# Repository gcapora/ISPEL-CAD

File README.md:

# Diseño de circuitos impresos del proyecto ISPEL

Autores: Guillermo Caporaletti y Alejandro Santari.
ISPEL Beta, Revisión 1.

En esta carpeta están los diseños de las placas del prototipo Beta 2024 de la Interfaz de Señales para Prácticas Educativas de Laboratorio (ISPEL). 

## Estructura de carpetas

- Docs: Incluye documentos de elaboración propia. Incluye listado de materiales.
- Info: Incluye bibliografía, hojas de datos, referencias y demás información que no es elaboración propia.
- PCB_Frente: PCB de botones y leds del frente del gabinete.
- PCB_Principal: PCB principal, sobre la cual va montada la placa Nuleao-144 de STM.

## Versiones

- Primera versión Beta corresponde al diseño presentado como parte del trabajo final de la Carrera de Especialización en Sistemas Embebidos de la FIUBA: [Versión 1 Beta](https://github.com/gcapora/ISPEL-CAD/releases/tag/v1-beta)

## Comentarios

- El diseño en PCB_Principal fue corregido tras construir el primer prototipo.
- Los archivos de PCB_Frente son orientativos y deben ser corregidos.

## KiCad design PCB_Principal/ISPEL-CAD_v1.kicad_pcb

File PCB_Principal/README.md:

Aquí van los archivos del proyecto PLACA PRINCIPAL que incluye:
- Fuente y tensión de referencia
- Amplificadores
- Búferes de entrada
- Señal de prueba

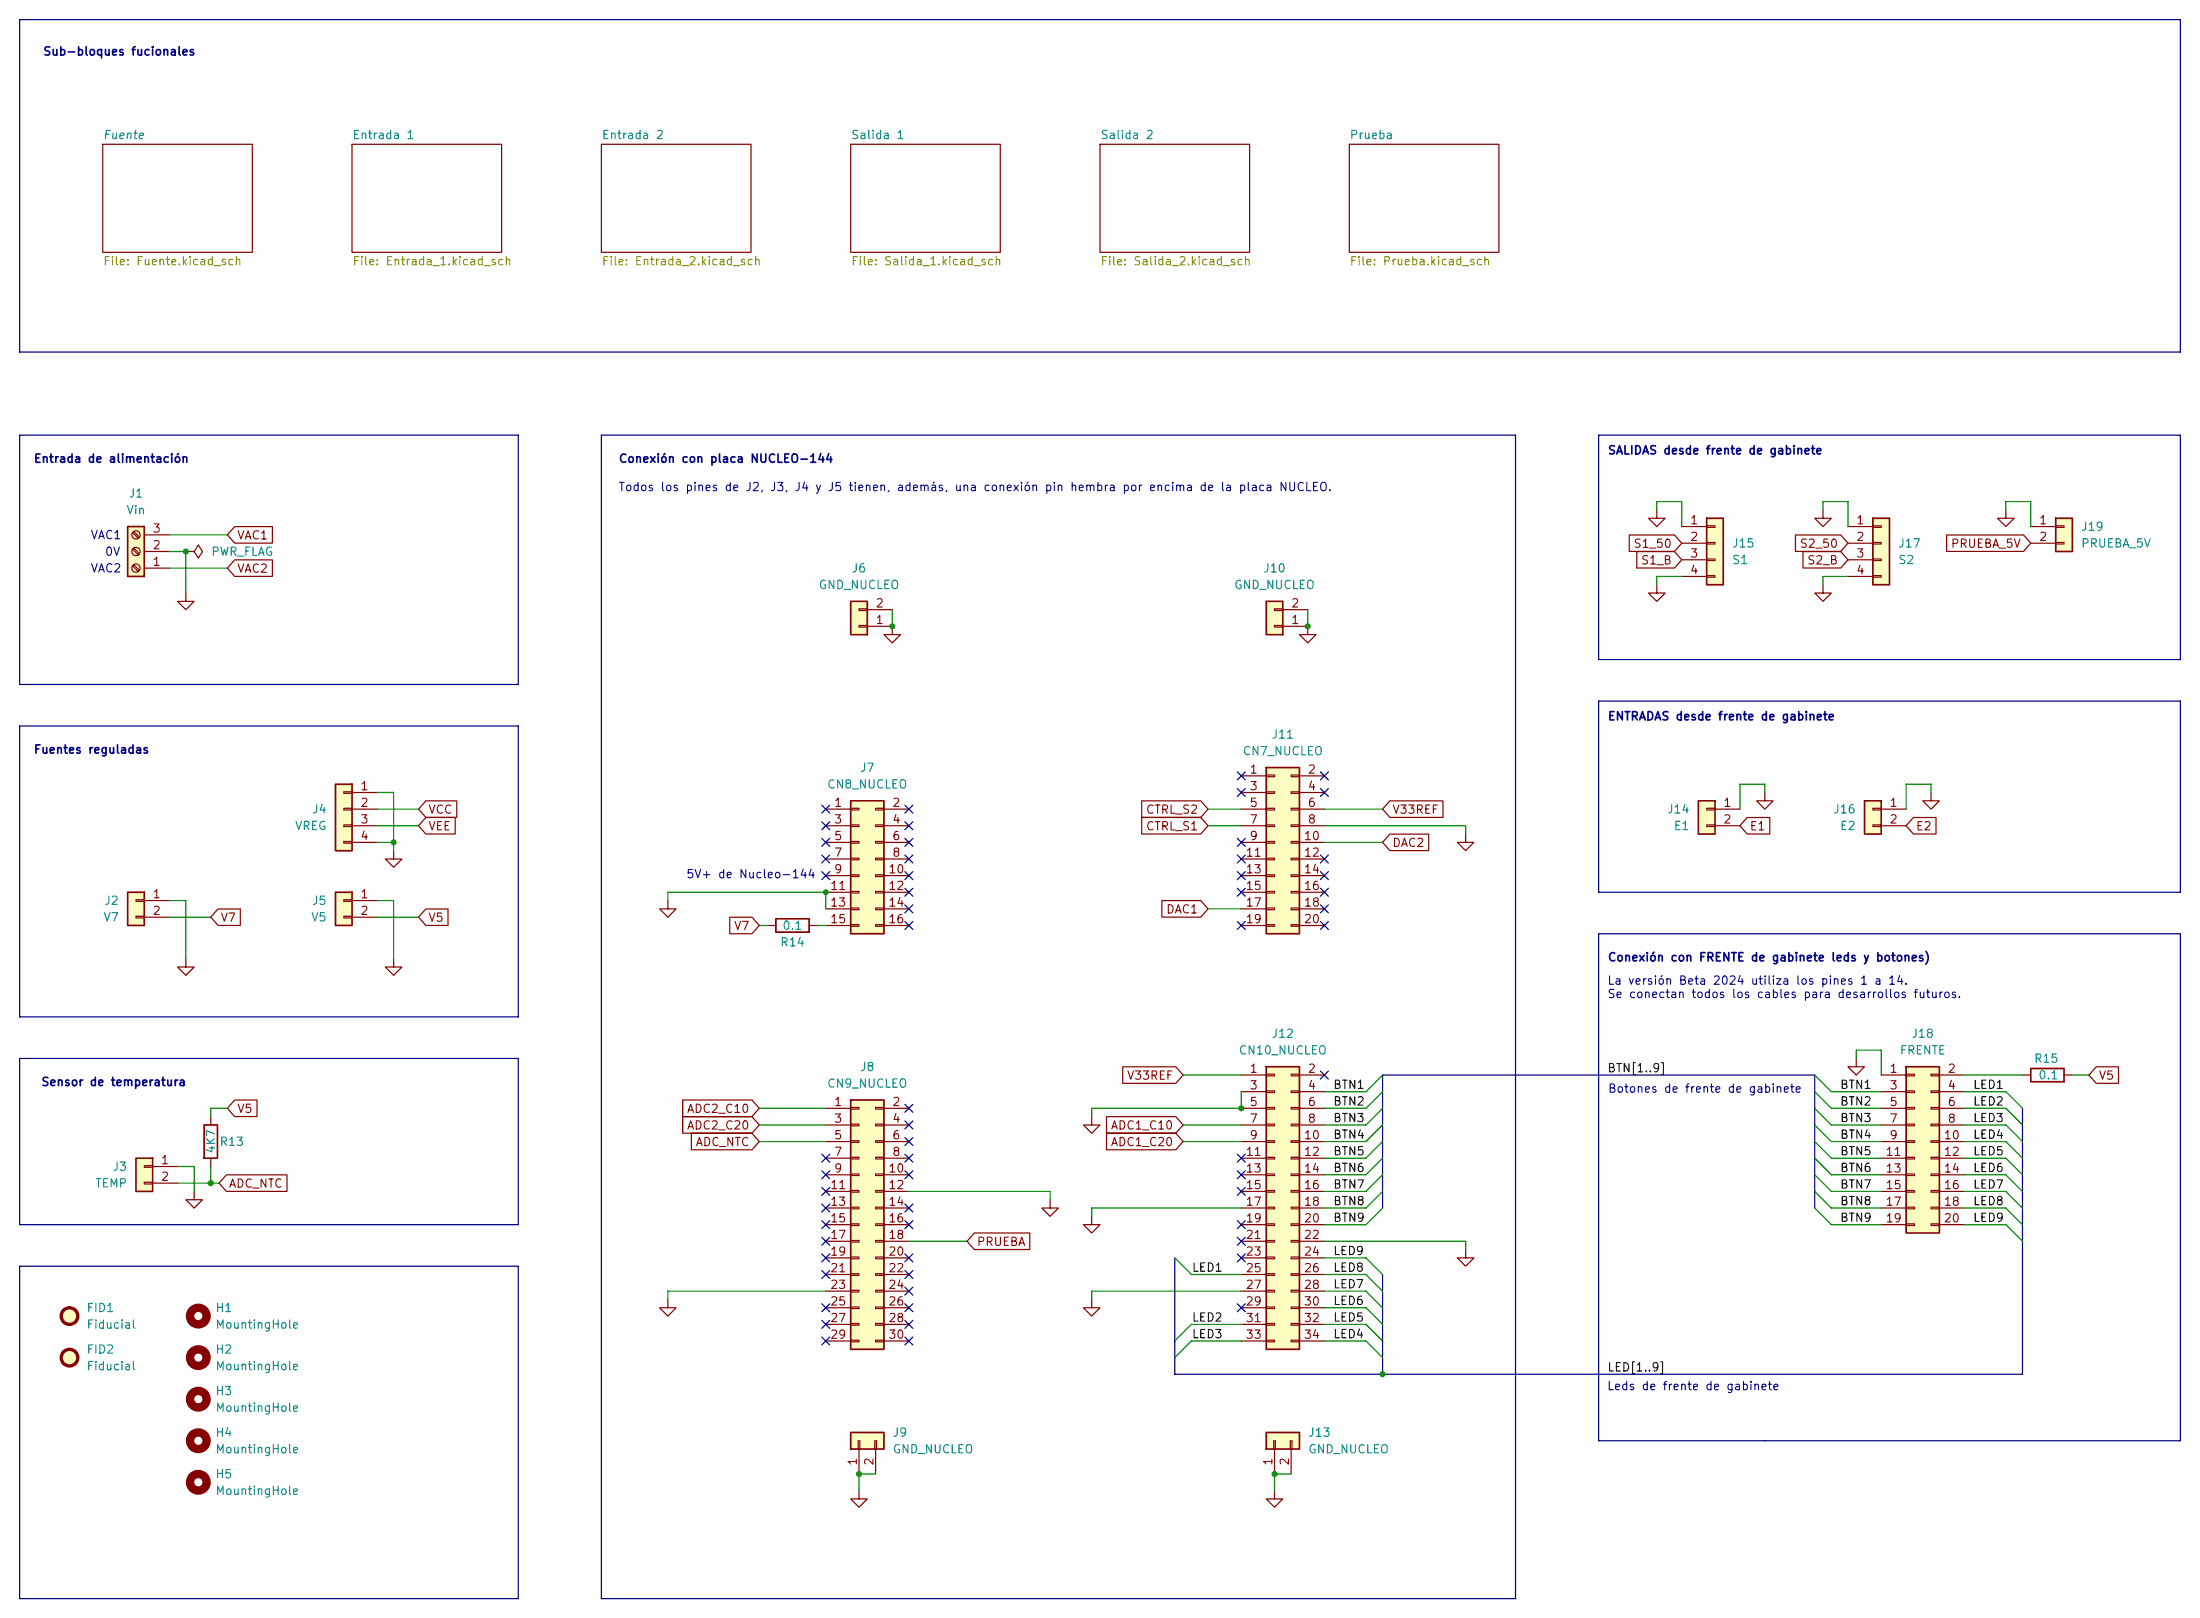
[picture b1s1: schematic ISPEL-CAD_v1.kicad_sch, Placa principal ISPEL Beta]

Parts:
FID1, FID2: Fiducial; Fiducial_1mm_Mask3mm
H1, H2, H3, H4, H5: MountingHole; MountingHole_3.2mm_M3
J1: Vin; TerminalBlock_Phoenix_MKDS-1,5-3-5.08_1x03_P5.08mm_Horizont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
J2: V7; PinSocket_1x02_P2.54mm_Vertical
J3: TEMP; PinHeader_1x02_P2.54mm_Vertical
J4: VREG; PinSocket_1x04_P2.54mm_Vertical
J5: V5; PinSocket_1x02_P2.54mm_Vertical
J6, J9, J10, J13: GND_NUCLEO; PinSocket_1x02_P2.54mm_Vertical
J7: CN8_NUCLEO; PinSocket_2x08_P2.54mm_Vertical_impar-par
J8: CN9_NUCLEO; PinSocket_2x15_P2.54mm_Vertical_impar-par
J11: CN7_NUCLEO; PinSocket_2x10_P2.54mm_Vertical_impar-par
J12: CN10_NUCLEO; PinSocket_2x17_P2.54mm_Vertical_impar-par
J14: E1; Molex_KK-254_AE-6410-02A_1x02_P2.54mm_Vertical
J15: S1; Molex_KK-254_AE-6410-04A_1x04_P2.54mm_Vertical
J16: E2; Molex_KK-254_AE-6410-02A_1x02_P2.54mm_Vertical
J17: S2; Molex_KK-254_AE-6410-04A_1x04_P2.54mm_Vertical
J18: FRENTE; IDC-Header_2x10_P2.54mm_Vertical
J19: PRUEBA_5V; Molex_KK-254_AE-6410-02A_1x02_P2.54mm_Vertical
R13: 4K7; R_1206_3216Metric_Pad1.30x1.75mm_HandSolder
R14, R15: 0.1; R_1206_3216Metric_Pad1.30x1.75mm_HandSolder

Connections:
/BTN1: J12.4, J18.3
/BTN2: J12.6, J18.5
/BTN3: J12.8, J18.7
/BTN4: J12.10, J18.9
/BTN5: J12.12, J18.11
/BTN6: J12.14, J18.13
/BTN7: J12.16, J18.15
/BTN8: J12.18, J18.17
/BTN9: J12.20, J18.19
/LED1: J12.25, J18.4
/LED2: J12.31, J18.6
/LED3: J12.33, J18.8
/LED4: J12.34, J18.10
/LED5: J12.32, J18.12
/LED6: J12.30, J18.14
/LED7: J12.28, J18.16
/LED8: J12.26, J18.18
/LED9: J12.24, J18.20
ADC1_C10: J12.7; also elsewhere on the board
ADC1_C20: J12.9; also elsewhere on the board
ADC2_C10: J8.1; also elsewhere on the board
ADC2_C20: J8.3; also elsewhere on the board
ADC_NTC: J3.2, J8.5, R13.2
CTRL_S1: J11.7; also elsewhere on the board
CTRL_S2: J11.5; also elsewhere on the board
DAC1: J11.17; also elsewhere on the board
DAC2: J11.10; also elsewhere on the board
E1: J14.2; also elsewhere on the board
E2: J16.2; also elsewhere on the board
GND: J1.2, J2.1, J3.1, J4.1, J4.4, J5.1, J6.1, J6.2, J7.11, J7.13, J8.12, J8.23, J9.1, J9.2, J10.1, J10.2, J11.8, J12.3, J12.5, J12.17, J12.22, J12.27, J13.1, J13.2, J14.1, J15.1, J15.4, J16.1, J17.1, J17.4, J18.1, J19.1; also elsewhere on the board
unnamed: J7.15, R14.2
unnamed: J18.2, R15.1
PRUEBA: J8.18; also elsewhere on the board
PRUEBA_5V: J19.2; also elsewhere on the board
S1_50: J15.2; also elsewhere on the board
S1_B: J15.3; also elsewhere on the board
S2_50: J17.2; also elsewhere on the board
S2_B: J17.3; also elsewhere on the board
V5: J5.2, R13.1, R15.2; also elsewhere on the board
V7: J2.2, R14.1; also elsewhere on the board
V33REF: J11.6, J12.1; also elsewhere on the board
VAC1: J1.3; also elsewhere on the board
VAC2: J1.1; also elsewhere on the board
VCC: J4.2; also elsewhere on the board
VEE: J4.3; also elsewhere on the board

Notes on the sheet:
5V+ de Nucleo-144
Conexión con FRENTE de gabinete leds y botones)
ENTRADAS desde frente de gabinete
Leds de frente de gabinete
VAC1
La versión Beta 2024 utiliza los pines 1 a 14. Se conectan todos los cables para desarrollos futuros.
Fuentes reguladas
Entrada de alimentación
Todos los pines de J2, J3, J4 y J5 tienen, además, una conexión pin hembra por encima de la placa NUCLEO.
Sub-bloques fucionales
Conexión con placa NUCLEO-144
Botones de frente de gabinete
VAC2
SALIDAS desde frente de gabinete
Sensor de temperatura

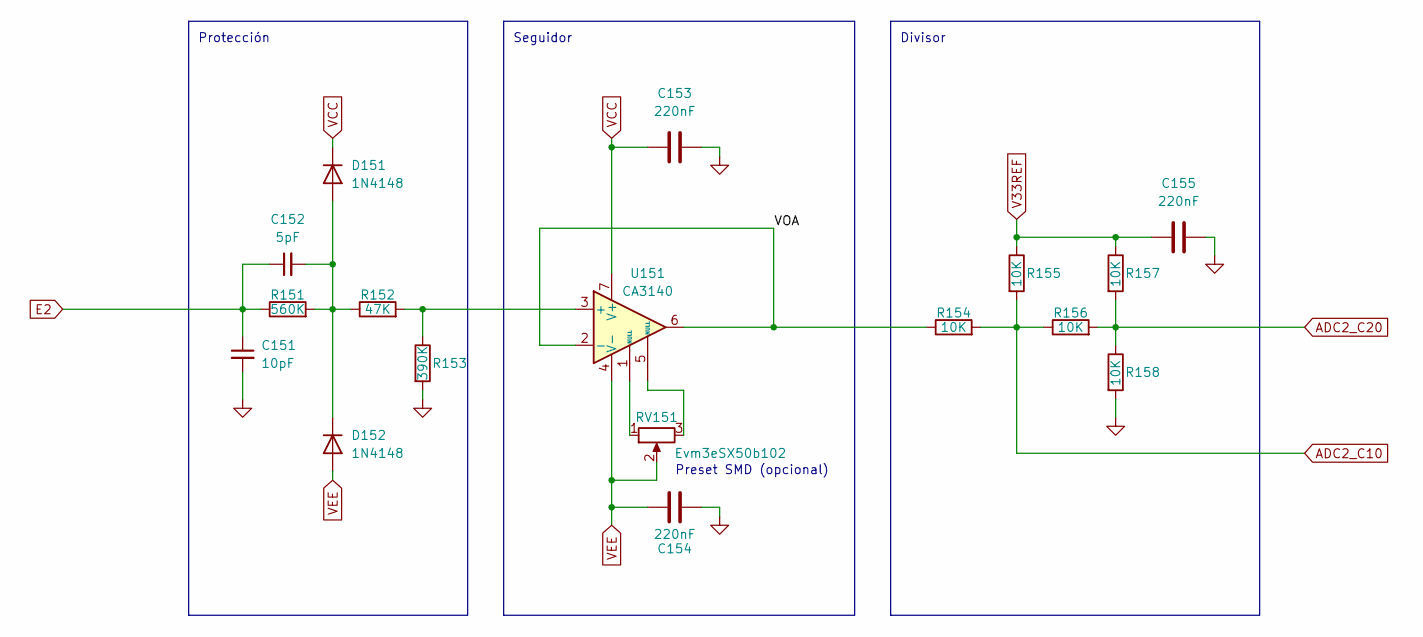
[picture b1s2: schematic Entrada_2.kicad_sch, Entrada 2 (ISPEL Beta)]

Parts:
C151: 10pF; C_1206_3216Metric_Pad1.33x1.80mm_HandSolder
C152: 5pF; C_1206_3216Metric_Pad1.33x1.80mm_HandSolder
C153, C154, C155: 220nF; C_1206_3216Metric_Pad1.33x1.80mm_HandSolder
D151, D152: 1N4148; D_MiniMELF_Handsoldering
R151: 560K; R_1206_3216Metric_Pad1.30x1.75mm_HandSolder
R152: 47K; R_1206_3216Metric_Pad1.30x1.75mm_HandSolder
R153: 390K; R_1206_3216Metric_Pad1.30x1.75mm_HandSolder
R154, R155, R156, R157, R158: 10K; R_1206_3216Metric_Pad1.30x1.75mm_HandSolder
RV151: Evm3eSX50b102; 3E-SX50
U151: CA3140; CERDIP-8_W7.62mm_SideBrazed_LongPads_Socket

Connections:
/Entrada 2/VOA: R154.1, U151.2 (-), U151.6
ADC2_C10: R154.2, R155.2, R156.1; also elsewhere on the board
ADC2_C20: R156.2, R157.2, R158.1; also elsewhere on the board
E2: C151.1, C152.1, R151.1; also elsewhere on the board
GND: C151.2, C153.2, C154.2, C155.2, R153.2, R158.2; also elsewhere on the board
unnamed: C152.2, D151.2 (A), D152.1 (K), R151.2, R152.1
unnamed: RV151.1, U151.1 (NULL)
unnamed: RV151.3, U151.5 (NULL)
unnamed: R152.2, R153.1, U151.3 (+)
V33REF: C155.1, R155.1, R157.1; also elsewhere on the board
VCC: C153.1, D151.1 (K), U151.7 (V+); also elsewhere on the board
VEE: C154.1, D152.2 (A), RV151.2, U151.4 (V-); also elsewhere on the board

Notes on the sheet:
Preset SMD (opcional)
Protección
Divisor
Seguidor

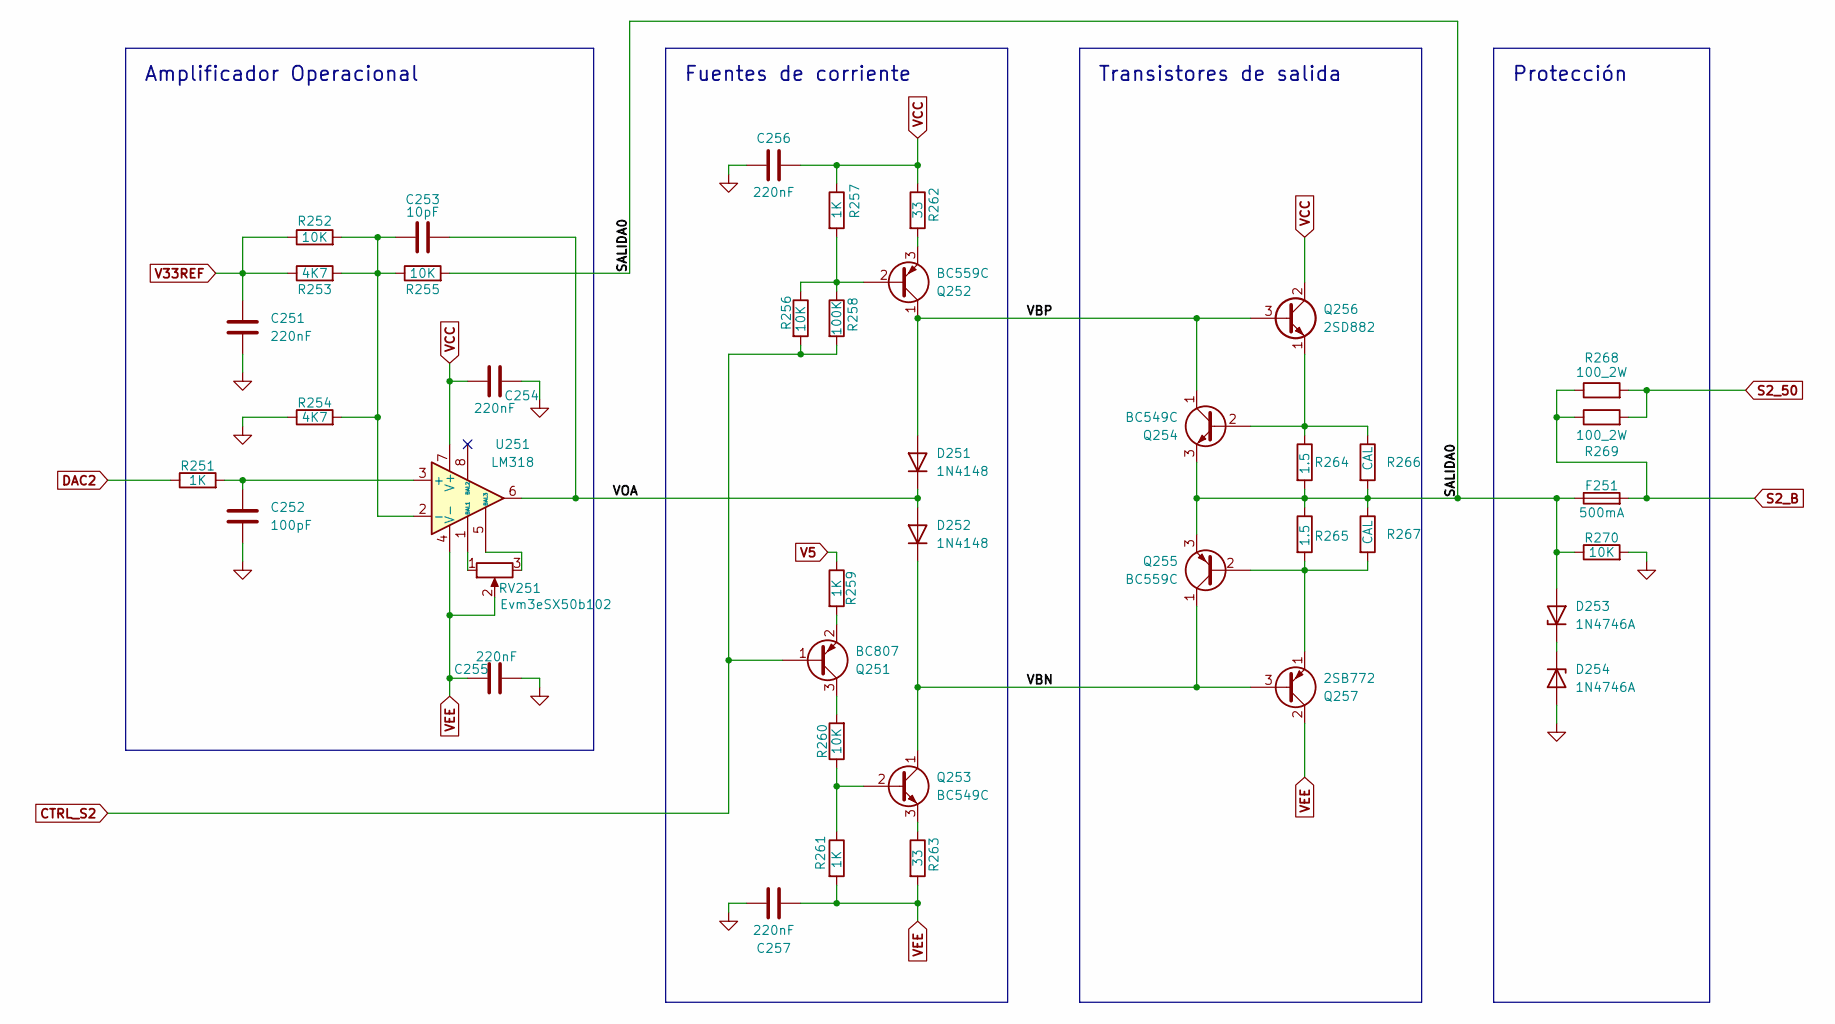
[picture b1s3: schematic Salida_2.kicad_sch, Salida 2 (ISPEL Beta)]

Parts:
C251, C254, C255, C256, C257: 220nF; C_1206_3216Metric_Pad1.33x1.80mm_HandSolder
C252: 100pF; C_1206_3216Metric_Pad1.33x1.80mm_HandSolder
C253: 10pF; C_1206_3216Metric_Pad1.33x1.80mm_HandSolder
D251, D252: 1N4148; D_MiniMELF_Handsoldering
D253, D254: 1N4746A; D_DO-41_SOD81_P10.16mm_Horizontal
F251: 500mA; Fuseholder_1808_handsoldering
Q251: BC807; SOT-23
Q252, Q255: BC559C; TO-92_Inline
Q253, Q254: BC549C; TO-92_Inline
Q256: 2SD882; TO-126-3_Vertical
Q257: 2SB772; TO-126-3_Vertical
R251, R257, R259, R261: 1K; R_1206_3216Metric_Pad1.30x1.75mm_HandSolder
R252, R255, R256, R260, R270: 10K; R_1206_3216Metric_Pad1.30x1.75mm_HandSolder
R253, R254: 4K7; R_1206_3216Metric_Pad1.30x1.75mm_HandSolder
R258: 100K; R_1206_3216Metric_Pad1.30x1.75mm_HandSolder
R262, R263: 33; R_1206_3216Metric_Pad1.30x1.75mm_HandSolder
R264, R265: 1.5; R_Axial_DIN0309_L9.0mm_D3.2mm_P12.70mm_Horizontal
R266, R267: CAL; R_1206_3216Metric_Pad1.30x1.75mm_HandSolder
R268, R269: 100_2W; R_Axial_DIN0414_L11.9mm_D4.5mm_P15.24mm_Horizontal
RV251: Evm3eSX50b102; 3E-SX50
U251: LM318; CERDIP-8_W7.62mm_SideBrazed_LongPads_Socket

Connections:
/Salida 2/SALIDA0: D253.2 (A), F251.1, Q254.3 (E), Q255.3 (E), R255.2, R264.2, R265.1, R266.2, R267.1, R270.1
/Salida 2/VBN: D252.1 (K), Q253.1 (C), Q255.1 (C), Q257.3 (B)
/Salida 2/VBP: D251.2 (A), Q252.1 (C), Q254.1 (C), Q256.3 (B)
/Salida 2/VOA: C253.2, D251.1 (K), D252.2 (A), U251.6
CTRL_S2: Q251.1 (B), R256.2, R258.2; also elsewhere on the board
DAC2: R251.1; also elsewhere on the board
GND: C251.2, C252.2, C254.1, C255.2, C256.2, C257.1, D254.2 (A), R254.1, R270.2; also elsewhere on the board
unnamed: D253.1 (K), D254.1 (K)
unnamed: Q251.3 (C), R260.2
unnamed: Q251.2 (E), R259.2
unnamed: Q252.2 (B), R256.1, R257.2, R258.1
unnamed: Q252.3 (E), R262.2
unnamed: Q253.2 (B), R260.1, R261.1
unnamed: Q253.3 (E), R263.1
unnamed: Q254.2 (B), Q256.1 (E), R264.1, R266.1
unnamed: Q255.2 (B), Q257.1 (E), R265.2, R267.2
unnamed: C252.1, R251.2, U251.3 (+)
unnamed: C253.1, R252.2, R253.2, R254.2, R255.1, U251.2 (-)
unnamed: RV251.1, U251.1 (BAL1)
unnamed: RV251.3, U251.5 (BAL3)
S2_50: R268.2, R269.2; also elsewhere on the board
S2_B: F251.2, R268.1, R269.1; also elsewhere on the board
V5: R259.1; also elsewhere on the board
V33REF: C251.1, R252.1, R253.1; also elsewhere on the board
VCC: C254.2, C256.1, Q256.2 (C), R257.1, R262.1, U251.7 (V+); also elsewhere on the board
VEE: C255.1, C257.2, Q257.2 (C), R261.2, R263.2, RV251.2, U251.4 (V-); also elsewhere on the board

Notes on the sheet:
Protección
Fuentes de corriente
Amplificador Operacional
Transistores de salida

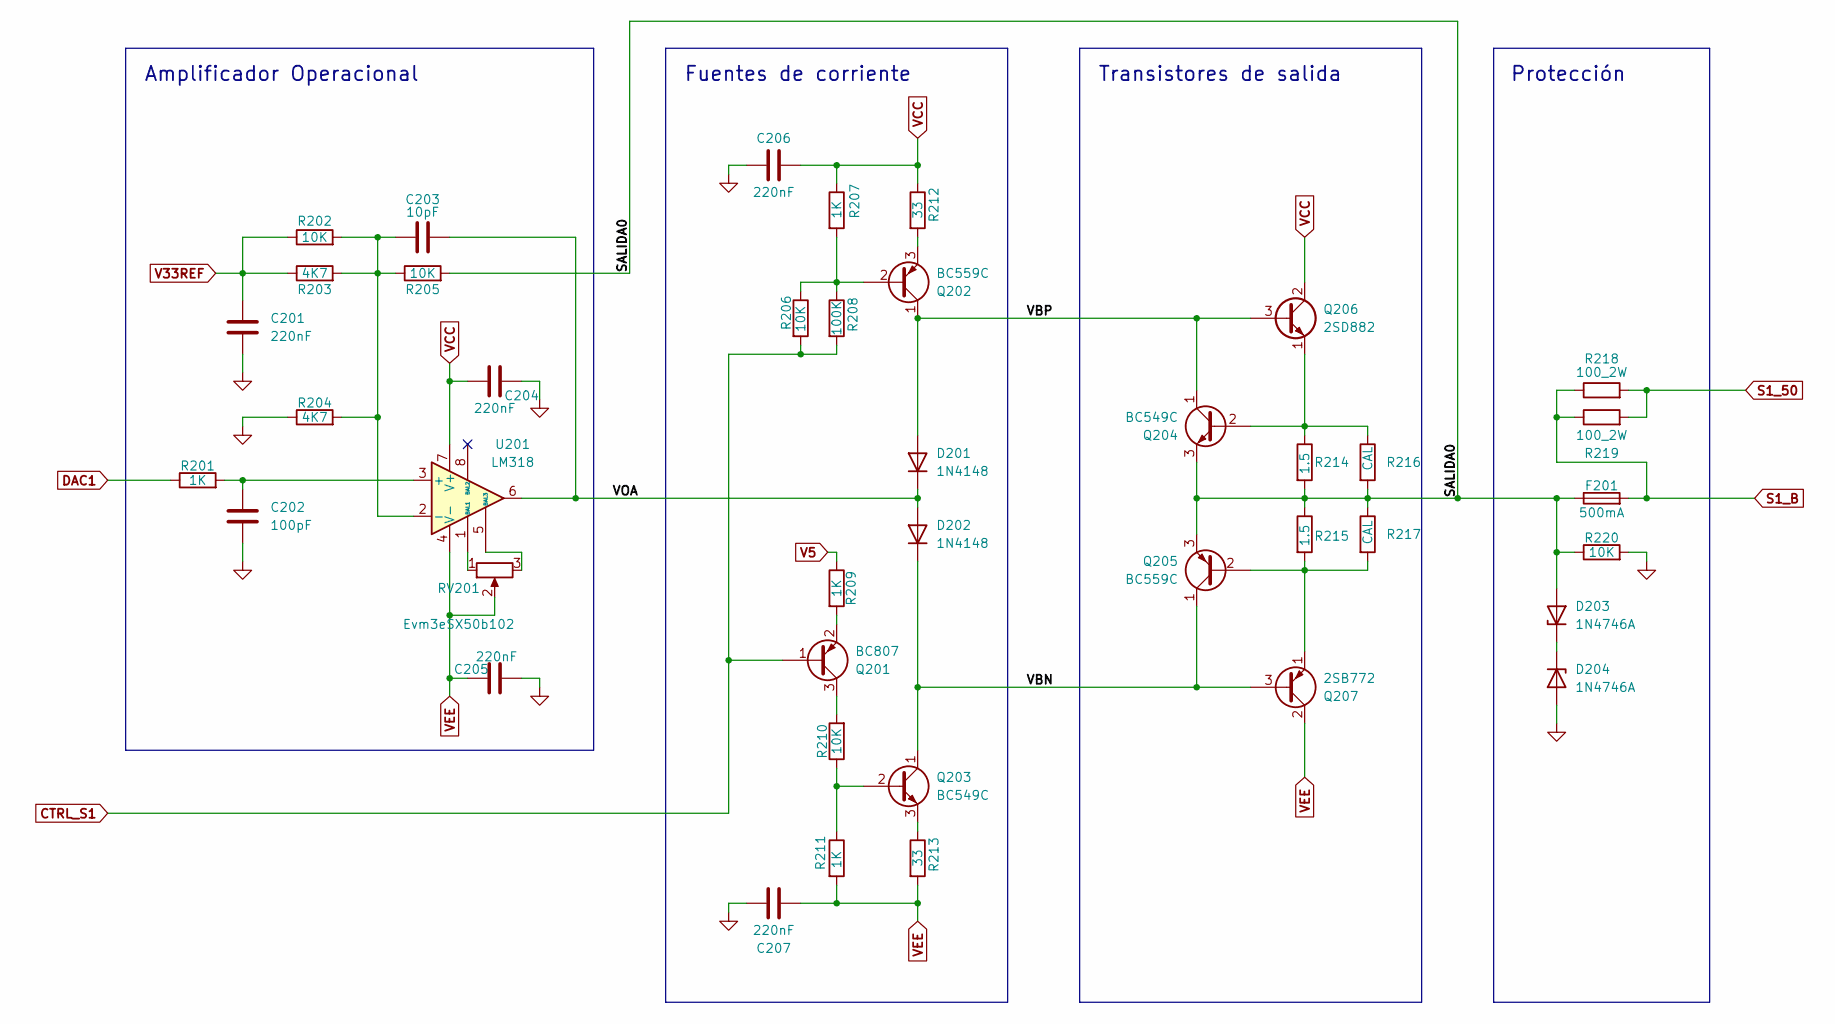
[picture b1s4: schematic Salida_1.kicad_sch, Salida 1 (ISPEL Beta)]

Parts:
C201, C204, C205, C206, C207: 220nF; C_1206_3216Metric_Pad1.33x1.80mm_HandSolder
C202: 100pF; C_1206_3216Metric_Pad1.33x1.80mm_HandSolder
C203: 10pF; C_1206_3216Metric_Pad1.33x1.80mm_HandSolder
D201, D202: 1N4148; D_MiniMELF_Handsoldering
D203, D204: 1N4746A; D_DO-41_SOD81_P10.16mm_Horizontal
F201: 500mA; Fuseholder_1808_handsoldering
Q201: BC807; SOT-23
Q202, Q205: BC559C; TO-92_Inline
Q203, Q204: BC549C; TO-92_Inline
Q206: 2SD882; TO-126-3_Vertical
Q207: 2SB772; TO-126-3_Vertical
R201, R207, R209, R211: 1K; R_1206_3216Metric_Pad1.30x1.75mm_HandSolder
R202, R205, R206, R210, R220: 10K; R_1206_3216Metric_Pad1.30x1.75mm_HandSolder
R203, R204: 4K7; R_1206_3216Metric_Pad1.30x1.75mm_HandSolder
R208: 100K; R_1206_3216Metric_Pad1.30x1.75mm_HandSolder
R212, R213: 33; R_1206_3216Metric_Pad1.30x1.75mm_HandSolder
R214, R215: 1.5; R_Axial_DIN0309_L9.0mm_D3.2mm_P12.70mm_Horizontal
R216, R217: CAL; R_1206_3216Metric_Pad1.30x1.75mm_HandSolder
R218, R219: 100_2W; R_Axial_DIN0414_L11.9mm_D4.5mm_P15.24mm_Horizontal
RV201: Evm3eSX50b102; 3E-SX50
U201: LM318; CERDIP-8_W7.62mm_SideBrazed_LongPads_Socket

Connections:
/Salida 1/SALIDA0: D203.2 (A), F201.1, Q204.3 (E), Q205.3 (E), R205.2, R214.2, R215.1, R216.2, R217.1, R220.1
/Salida 1/VBN: D202.1 (K), Q203.1 (C), Q205.1 (C), Q207.3 (B)
/Salida 1/VBP: D201.2 (A), Q202.1 (C), Q204.1 (C), Q206.3 (B)
/Salida 1/VOA: C203.2, D201.1 (K), D202.2 (A), U201.6
CTRL_S1: Q201.1 (B), R206.2, R208.2; also elsewhere on the board
DAC1: R201.1; also elsewhere on the board
GND: C201.2, C202.2, C204.1, C205.2, C206.2, C207.1, D204.2 (A), R204.1, R220.2; also elsewhere on the board
unnamed: D203.1 (K), D204.1 (K)
unnamed: Q201.3 (C), R210.2
unnamed: Q201.2 (E), R209.2
unnamed: Q202.2 (B), R206.1, R207.2, R208.1
unnamed: Q202.3 (E), R212.2
unnamed: Q203.2 (B), R210.1, R211.1
unnamed: Q203.3 (E), R213.1
unnamed: Q204.2 (B), Q206.1 (E), R214.1, R216.1
unnamed: Q205.2 (B), Q207.1 (E), R215.2, R217.2
unnamed: C202.1, R201.2, U201.3 (+)
unnamed: C203.1, R202.2, R203.2, R204.2, R205.1, U201.2 (-)
unnamed: RV201.1, U201.1 (BAL1)
unnamed: RV201.3, U201.5 (BAL3)
S1_50: R218.2, R219.2; also elsewhere on the board
S1_B: F201.2, R218.1, R219.1; also elsewhere on the board
V5: R209.1; also elsewhere on the board
V33REF: C201.1, R202.1, R203.1; also elsewhere on the board
VCC: C204.2, C206.1, Q206.2 (C), R207.1, R212.1, U201.7 (V+); also elsewhere on the board
VEE: C205.1, C207.2, Q207.2 (C), R211.2, R213.2, RV201.2, U201.4 (V-); also elsewhere on the board

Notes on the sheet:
Protección
Fuentes de corriente
Amplificador Operacional
Transistores de salida

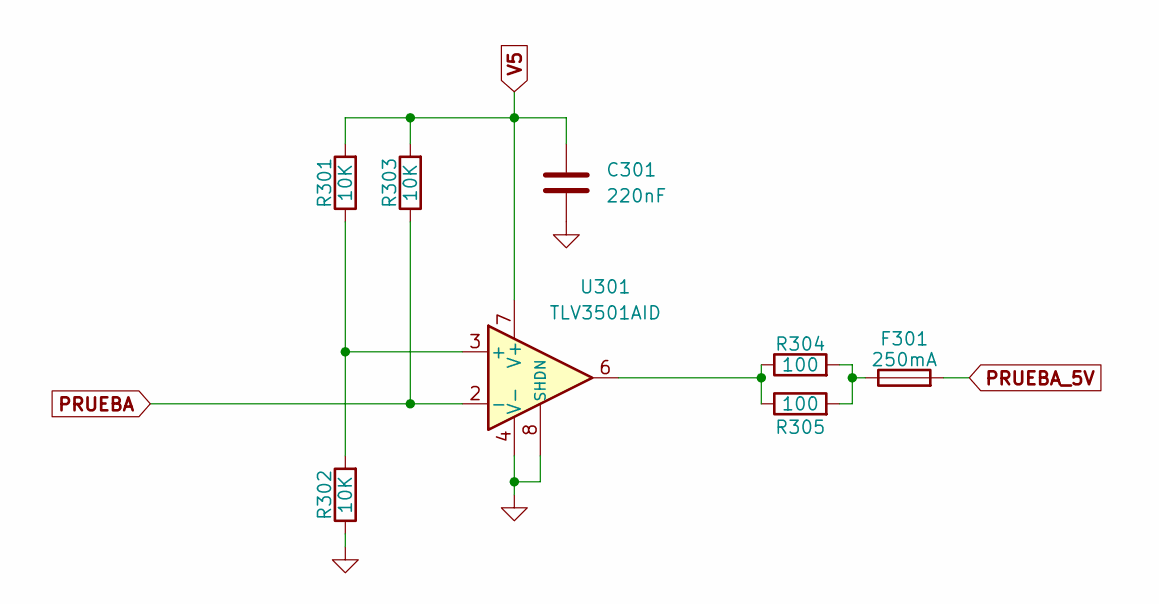
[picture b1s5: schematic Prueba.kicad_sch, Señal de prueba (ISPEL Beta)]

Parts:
C301: 220nF; C_1206_3216Metric_Pad1.33x1.80mm_HandSolder
F301: 250mA; Fuseholder_1808_handsoldering
R301, R302, R303: 10K; R_1206_3216Metric_Pad1.30x1.75mm_HandSolder
R304, R305: 100; R_1206_3216Metric_Pad1.30x1.75mm_HandSolder
U301: TLV3501AID; SOIC-8_3.9x4.9mm_P1.27mm

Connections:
GND: C301.1, R302.1, U301.4 (V-), U301.8 (SHDN); also elsewhere on the board
unnamed: F301.1, R304.2, R305.2
unnamed: R304.1, R305.1, U301.6
unnamed: R301.1, R302.2, U301.3 (+)
PRUEBA: R303.1, U301.2 (-); also elsewhere on the board
PRUEBA_5V: F301.2; also elsewhere on the board
V5: C301.2, R301.2, R303.2, U301.7 (V+); also elsewhere on the board

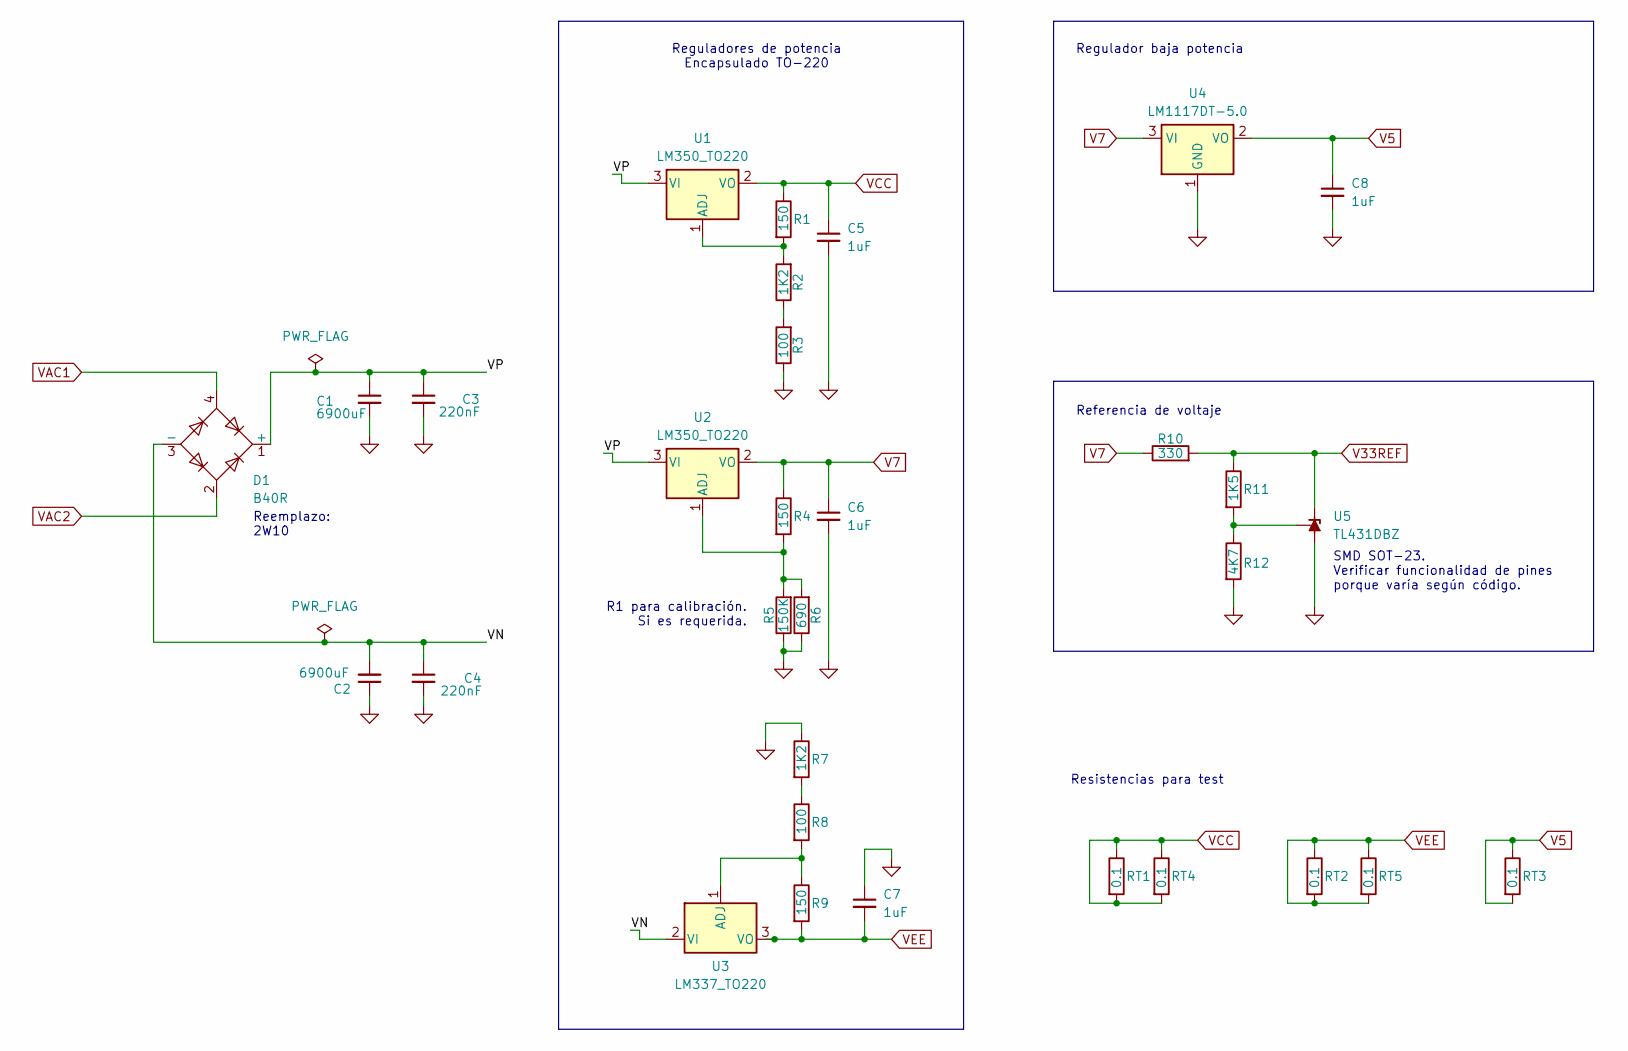
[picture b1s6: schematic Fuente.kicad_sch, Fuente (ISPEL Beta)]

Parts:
C1, C2: 6900uF; CP_Radial_D18.0mm_P7.50mm
C3, C4: 220nF; C_1206_3216Metric_Pad1.33x1.80mm_HandSolder
C5, C6, C7, C8: 1uF; C_1206_3216Metric_Pad1.33x1.80mm_HandSolder
D1: B40R; Diode_Bridge_Round_D9.0mm
R1, R4, R9: 150; R_1206_3216Metric_Pad1.30x1.75mm_HandSolder
R2, R7: 1K2; R_1206_3216Metric_Pad1.30x1.75mm_HandSolder
R3, R8: 100; R_1206_3216Metric_Pad1.30x1.75mm_HandSolder
R5: 150K; R_1206_3216Metric_Pad1.30x1.75mm_HandSolder
R6: 690; R_1206_3216Metric_Pad1.30x1.75mm_HandSolder
R10: 330; R_1206_3216Metric_Pad1.30x1.75mm_HandSolder
R11: 1K5; R_1206_3216Metric_Pad1.30x1.75mm_HandSolder
R12: 4K7; R_1206_3216Metric_Pad1.30x1.75mm_HandSolder
RT1, RT2, RT3, RT4, RT5: 0.1; R_1206_3216Metric_Pad1.30x1.75mm_HandSolder
U1, U2: LM350_TO220; TO-220-3_Vertical
U3: LM337_TO220; TO-220-3_Vertical
U4: LM1117DT-5.0; TO-252-3_TabPin2
U5: TL431DBZ; SOT-23

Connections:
/Fuente/VN: C2.2, C4.1, D1.3 (-), U3.2 (VI)
/Fuente/VP: C1.1, C3.1, D1.1 (+), U1.3 (VI), U2.3 (VI)
GND: C1.2, C2.1, C3.2, C4.2, C5.2, C6.2, C7.1, C8.2, R3.1, R5.1, R6.1, R7.1, R12.2, U4.1 (GND), U5.3 (A); also elsewhere on the board
unnamed: R2.1, R3.2
unnamed: R7.2, R8.1
unnamed: R1.2, R2.2, U1.1 (ADJ)
unnamed: R4.2, R5.2, R6.2, U2.1 (ADJ)
unnamed: R8.2, R9.1, U3.1 (ADJ)
unnamed: R11.2, R12.1, U5.2 (REF)
V5: C8.1, RT3.1, RT3.2, U4.2 (VO); also elsewhere on the board
V7: C6.1, R4.1, R10.1, U2.2 (VO), U4.3 (VI); also elsewhere on the board
V33REF: R10.2, R11.1, U5.1 (K); also elsewhere on the board
VAC1: D1.4; also elsewhere on the board
VAC2: D1.2; also elsewhere on the board
VCC: C5.1, R1.1, RT1.1, RT1.2, RT4.1, RT4.2, U1.2 (VO); also elsewhere on the board
VEE: C7.2, R9.2, RT2.1, RT2.2, RT5.1, RT5.2, U3.3 (VO); also elsewhere on the board

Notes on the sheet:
SMD SOT-23. Verificar funcionalidad de pines porque varía según código.
Reemplazo: 2W10
R1 para calibración. Si es requerida.
Referencia de voltaje
Reguladores de potencia Encapsulado TO-220
Resistencias para test
Regulador baja potencia

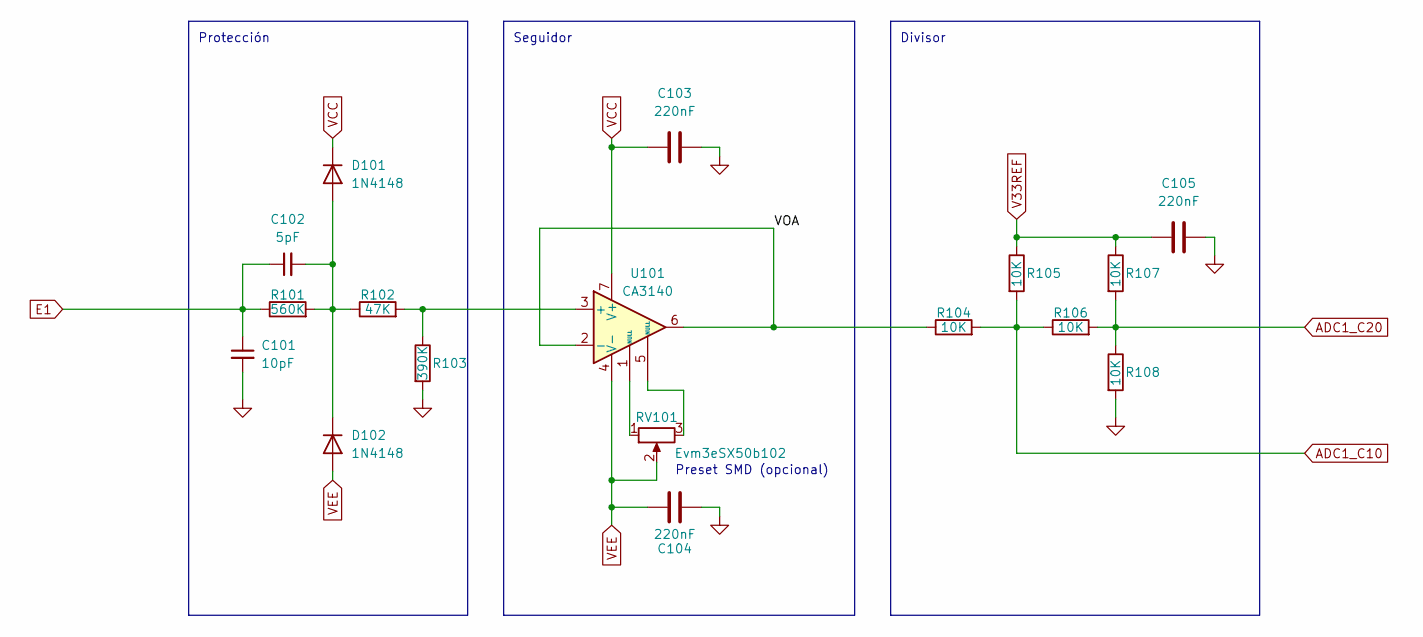
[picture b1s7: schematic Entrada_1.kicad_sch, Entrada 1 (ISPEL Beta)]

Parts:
C101: 10pF; C_1206_3216Metric_Pad1.33x1.80mm_HandSolder
C102: 5pF; C_1206_3216Metric_Pad1.33x1.80mm_HandSolder
C103, C104, C105: 220nF; C_1206_3216Metric_Pad1.33x1.80mm_HandSolder
D101, D102: 1N4148; D_MiniMELF_Handsoldering
R101: 560K; R_1206_3216Metric_Pad1.30x1.75mm_HandSolder
R102: 47K; R_1206_3216Metric_Pad1.30x1.75mm_HandSolder
R103: 390K; R_1206_3216Metric_Pad1.30x1.75mm_HandSolder
R104, R105, R106, R107, R108: 10K; R_1206_3216Metric_Pad1.30x1.75mm_HandSolder
RV101: Evm3eSX50b102; 3E-SX50
U101: CA3140; CERDIP-8_W7.62mm_SideBrazed_LongPads_Socket

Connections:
/Entrada 1/VOA: R104.1, U101.2 (-), U101.6
ADC1_C10: R104.2, R105.2, R106.1; also elsewhere on the board
ADC1_C20: R106.2, R107.2, R108.1; also elsewhere on the board
E1: C101.1, C102.1, R101.1; also elsewhere on the board
GND: C101.2, C103.2, C104.2, C105.2, R103.2, R108.2; also elsewhere on the board
unnamed: C102.2, D101.2 (A), D102.1 (K), R101.2, R102.1
unnamed: RV101.1, U101.1 (NULL)
unnamed: RV101.3, U101.5 (NULL)
unnamed: R102.2, R103.1, U101.3 (+)
V33REF: C105.1, R105.1, R107.1; also elsewhere on the board
VCC: C103.1, D101.1 (K), U101.7 (V+); also elsewhere on the board
VEE: C104.1, D102.2 (A), RV101.2, U101.4 (V-); also elsewhere on the board

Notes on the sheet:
Preset SMD (opcional)
Protección
Divisor
Seguidor

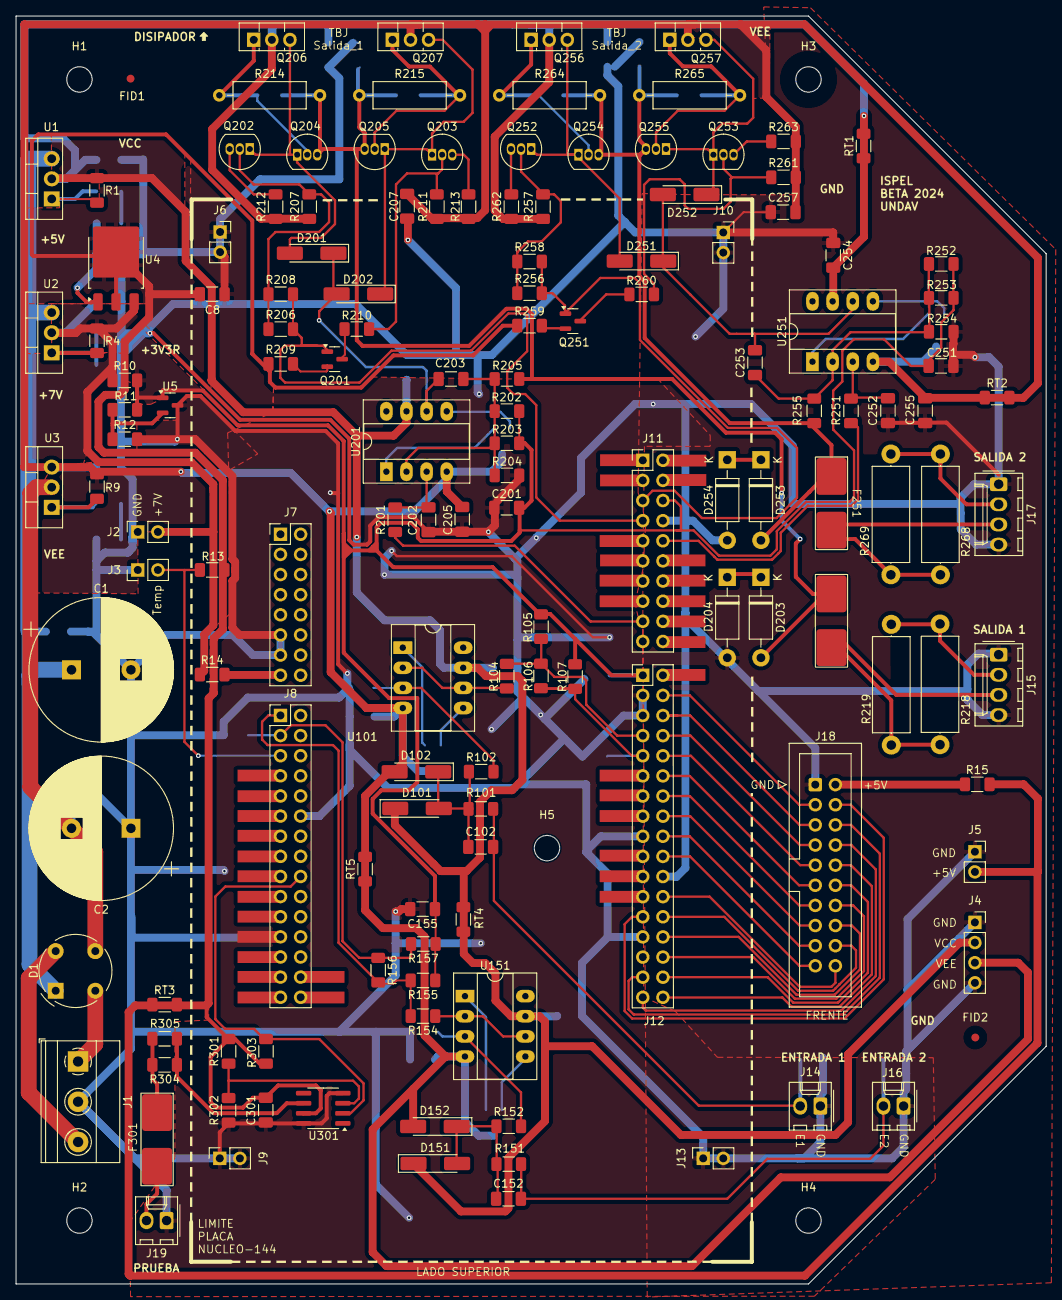
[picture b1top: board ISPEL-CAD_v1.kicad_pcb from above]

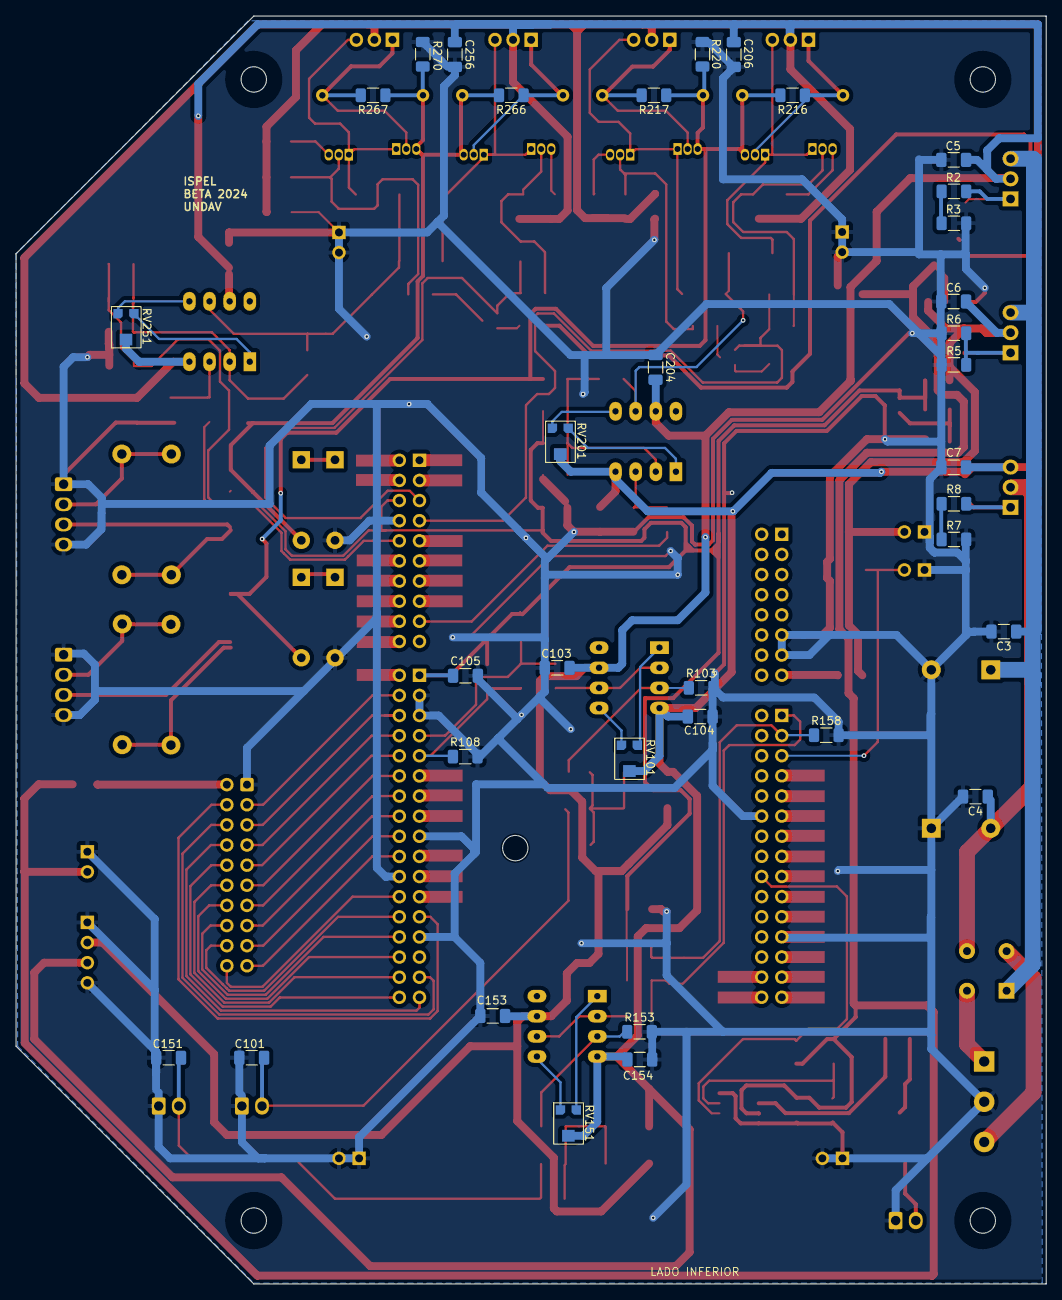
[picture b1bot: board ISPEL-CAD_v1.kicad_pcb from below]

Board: 2 copper layers, 130.0 x 160.0 mm, 184 parts (35 on the bottom side), 100 nets.
